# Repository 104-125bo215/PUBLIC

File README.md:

echo "# PUBLIC" >> README.md
git init
git add README.md
git commit -m "first commit"
git remote add origin https://github.com/104-125bo215/PUBLIC.git
git push -u origin master

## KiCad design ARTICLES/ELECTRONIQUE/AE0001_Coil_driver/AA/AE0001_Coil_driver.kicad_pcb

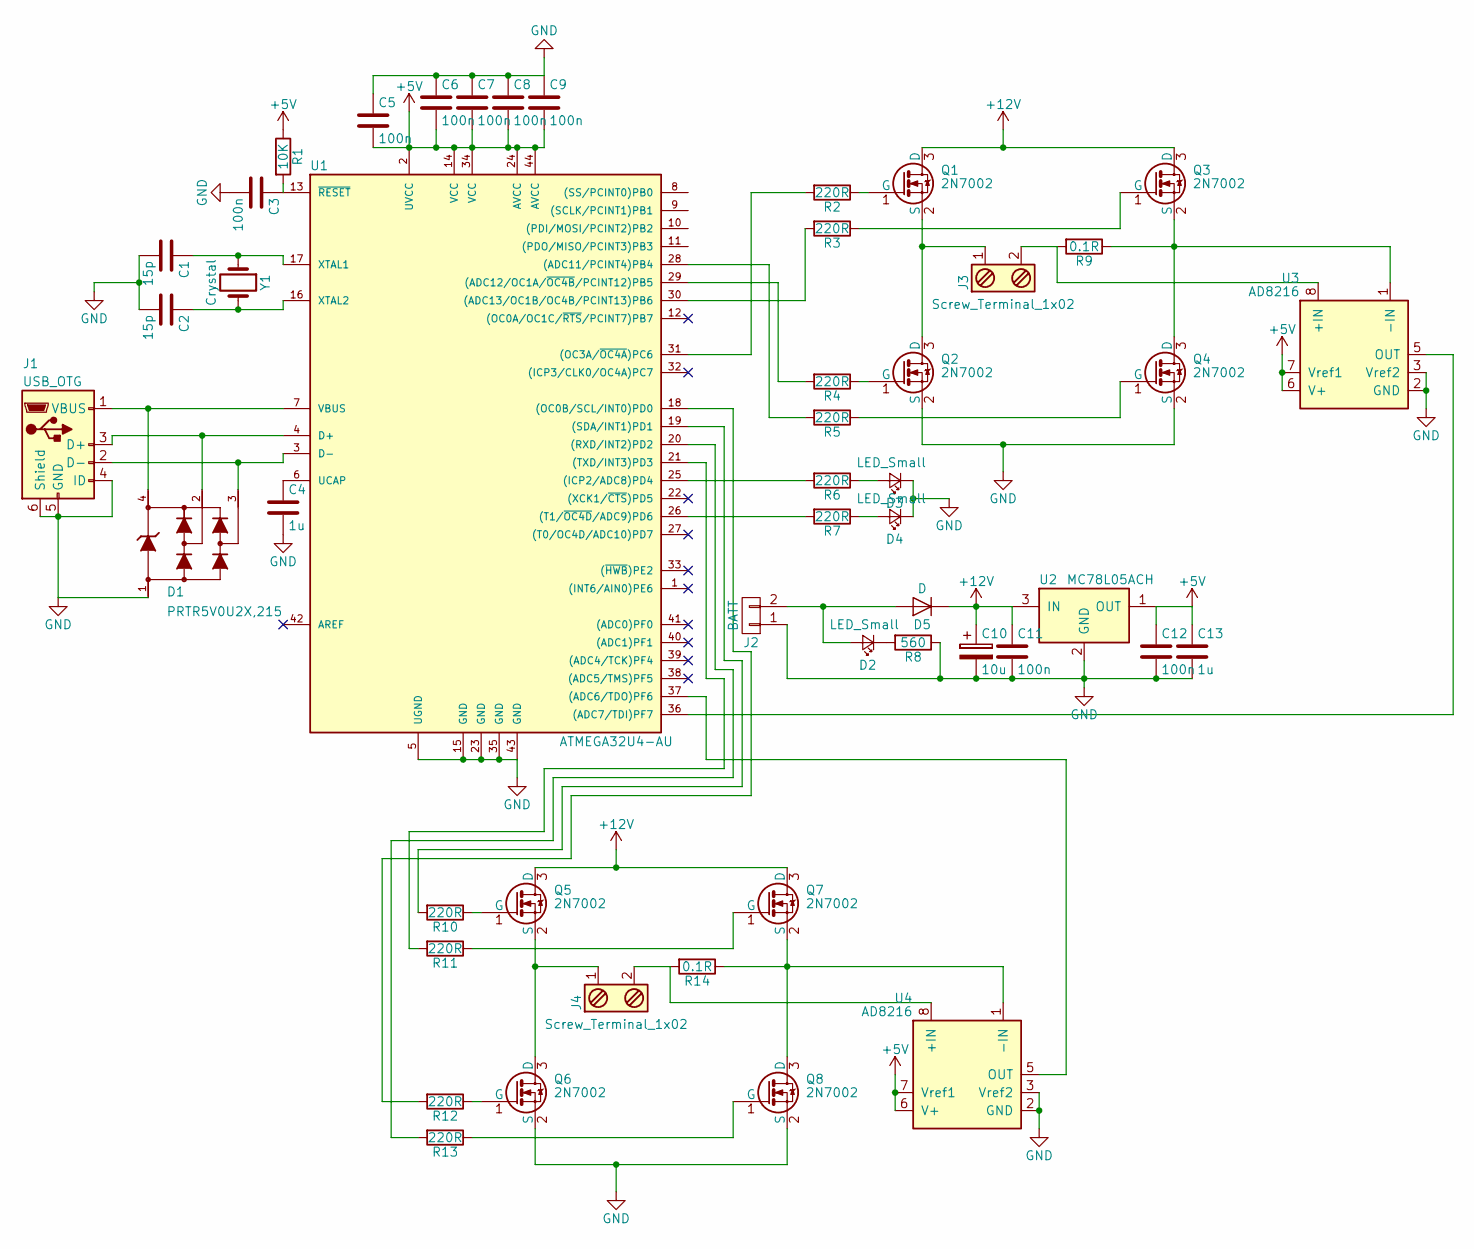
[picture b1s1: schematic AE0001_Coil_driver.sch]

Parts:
C1, C2: 15p; C_0603
C3, C5, C6, C9, C11, C12: 100n; C_0603
C4, C13: 1u; C_0603
C7, C8: 100n; C_0603_HandSoldering
C10: 10u; CP_Elec_6.3x4.5
D1: PRTR5V0U2X,215
D2, D3, D4: LED_Small; LED_0603
D5: D; D_0603
J1: USB_OTG; USB_Micro-B
J2: BATT; Pin_Header_Straight_1x02_Pitch1.00mm_SMD_Pin1Right
J3, J4: Screw_Terminal_1x02; bornier2
Q1, Q2, Q3, Q4, Q5, Q6, Q7, Q8: 2N7002; SOT-23
R1: 10K; R_0603
R2, R3, R4, R5, R6, R7, R10, R11, R12, R13: 220R; R_0603
R8: 560; R_0603
R9, R14: 0.1R; R_0603
U1: ATMEGA32U4-AU; TQFP-44_10x10mm_Pitch0.8mm
U2: MC78L05ACH; SOT-23
U3, U4: AD8216; SOIC-8_3.9x4.9mm_Pitch1.27mm
Y1: Crystal; Crystal_SMD_MicroCrystal_CC8V-T1A-2pin_2.0x1.2mm

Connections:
+5V: C5.2, C6.2, C7.2, C8.2, C9.2, C12.1, C13.1, R1.1, U1.2 (UVCC), U1.14 (VCC), U1.24 (AVCC), U1.34 (VCC), U1.44 (AVCC), U2.1 (OUT), U3.6 (V+), U3.7 (Vref1), U4.6 (V+), U4.7 (Vref1)
+12V: C10.1, C11.1, D5.1 (K), Q1.3 (D), Q3.3 (D), Q5.3 (D), Q7.3 (D), U2.3 (IN)
GND: C1.2, C2.2, C3.2, C4.2, C5.1, C6.1, C7.1, C8.1, C9.1, C10.2, C11.2, C12.2, C13.2, D1.1, D3.1 (K), D4.1 (K), J1.4 (ID), J1.5 (GND), J1.6 (Shield), J2.1, Q2.2 (S), Q4.2 (S), Q6.2 (S), Q8.2 (S), R8.1, U1.5 (UGND), U1.15 (GND), U1.23 (GND), U1.35 (GND), U1.43 (GND), U2.2 (GND), U3.2 (GND), U3.3 (Vref2), U4.2 (GND), U4.3 (Vref2)
unnamed: C1.1, U1.17 (XTAL1), Y1.1
unnamed: C2.1, U1.16 (XTAL2), Y1.2
unnamed: C3.1, R1.2, U1.13 (~RESET~)
unnamed: C4.1, U1.6 (UCAP)
unnamed: D1.2, J1.3 (D+), U1.4 (D+)
unnamed: D1.3, J1.2 (D-), U1.3 (D-)
unnamed: D1.4, J1.1 (VBUS), U1.7 (VBUS)
unnamed: D2.1 (K), R8.2
unnamed: D2.2 (A), D5.2 (A), J2.2
unnamed: D3.2 (A), R6.1
unnamed: D4.2 (A), R7.1
unnamed: J3.1, Q1.2 (S), Q2.3 (D)
unnamed: J3.2, R9.2, U3.8 (+IN)
unnamed: J4.1, Q5.2 (S), Q6.3 (D)
unnamed: J4.2, R14.2, U4.8 (+IN)
unnamed: Q1.1 (G), R2.1
unnamed: Q2.1 (G), R4.1
unnamed: Q3.1 (G), R3.1
unnamed: Q3.2 (S), Q4.3 (D), R9.1, U3.1 (-IN)
unnamed: Q4.1 (G), R5.1
unnamed: Q5.1 (G), R10.1
unnamed: Q6.1 (G), R12.1
unnamed: Q7.1 (G), R11.1
unnamed: Q7.2 (S), Q8.3 (D), R14.1, U4.1 (-IN)
unnamed: Q8.1 (G), R13.1
unnamed: R2.2, U1.31 ((OC3A/~OC4A~)PC6)
unnamed: R3.2, U1.30 ((ADC13/OC1B/OC4B/PCINT13)PB6)
unnamed: R4.2, U1.29 ((ADC12/OC1A/~OC4B~/PCINT12)PB5)
unnamed: R5.2, U1.28 ((ADC11/PCINT4)PB4)
unnamed: R6.2, U1.25 ((ICP2/ADC8)PD4)
unnamed: R7.2, U1.26 ((T1/~OC4D~/ADC9)PD6)
unnamed: R10.2, U1.19 ((SDA/INT1)PD1)
unnamed: R11.2, U1.21 ((TXD/INT3)PD3)
unnamed: R12.2, U1.18 ((OC0B/SCL/INT0)PD0)
unnamed: R13.2, U1.20 ((RXD/INT2)PD2)
unnamed: U1.36 ((ADC7/TDI)PF7), U3.5 (OUT)
unnamed: U1.37 ((ADC6/TDO)PF6), U4.5 (OUT)

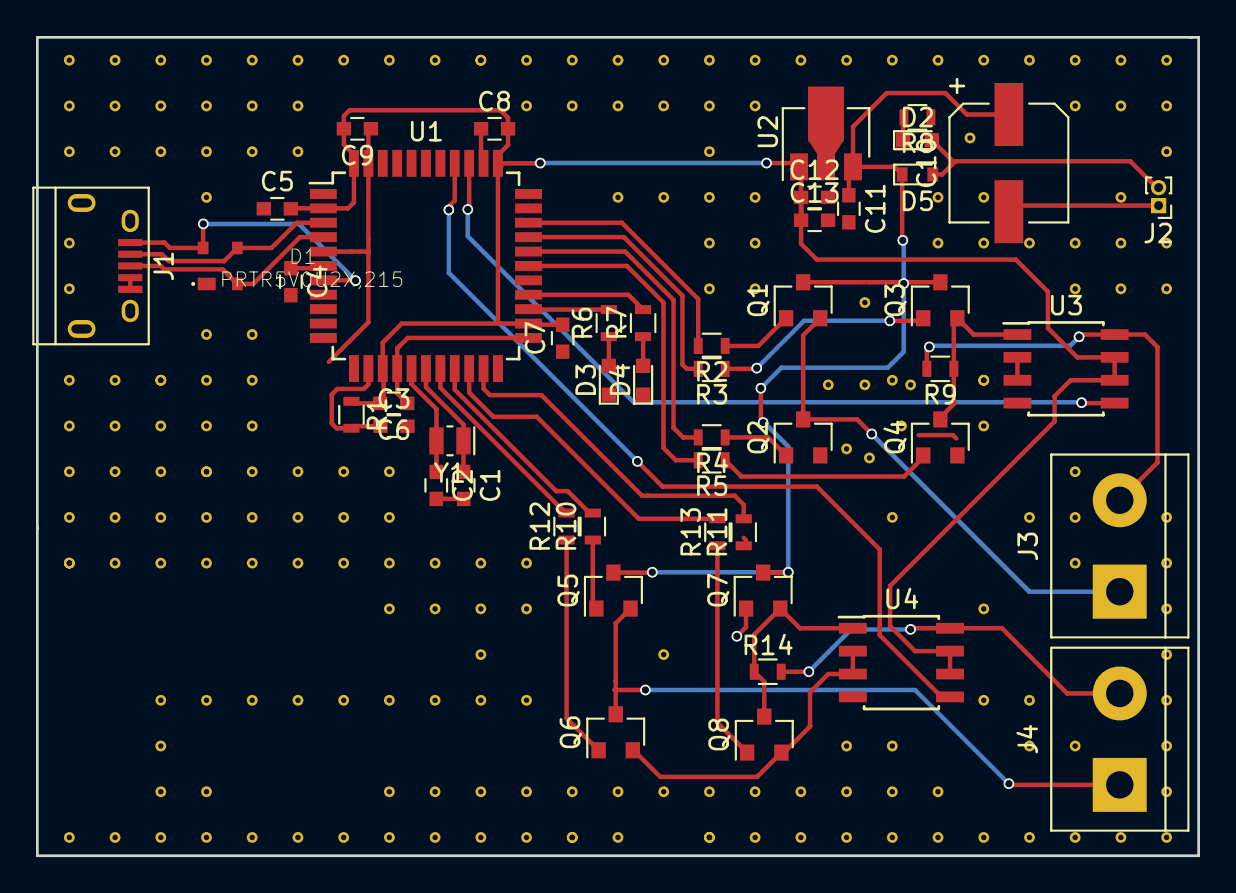
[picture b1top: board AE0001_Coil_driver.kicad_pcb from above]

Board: 2 copper layers, 64.5 x 45.5 mm, 49 parts (0 on the bottom side), 40 nets.
